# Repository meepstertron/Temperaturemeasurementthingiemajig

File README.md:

# Temperaturemeasurementthingimajig

That was a mouthful!

This is one of my first fully designed and hopefully made pcbs! :D

basically this is a small sensor node based on the readily availible CH32V003 which is a low cost (~20 cents!) risc-v MCU. it features a feature rich IO (well for 0.2usd it is). I am using the SHT4x chip to actually capture the environmental readings, because it is both accurate and fairly cost effective.

## Why should you care?

Honestly... You probably shouldnt, but for those who do want to know why: the whole node is open source meaning it can be re-mixed, re-branded and changed to your hearts content maybe even slap your logo or a silly cat on the silkscreen, it is also very cheap. running off a cr2032 and only costing about 3usd per node! Now compare that to the shelly series of Humid+Temp nodes...

## How is it so cheap??

I got it down to a nice value because i didnt use a expensive MCU like the ESP32 series (even though they are pretty effective in cost if you want wifi) but instead a cheaper and more bare bones MCU, since my project just didnt need it! a simple ASK/OOK transmitter instead of a costly variable or even wifi chip brought it down a lot as well. (we're talking cents but who cares)

## Bill of materials! (yall gotta foot the bill on this one :P /satire)
| Quantity | Component / Description | Package / Size | Estimated Cost (USD)
| :---: | :--- | :--- | :--- |
| **1x** | CR2032 Coin Cell Battery Holder | Through-Hole | 0.13 |
| **1x** | WCH CH32V003F4P6 Microcontroller | TSSOP-20 | 0.28 |
| **1x** | CMT2119A RF Transmitter | SOT-23-6 | 0.58 |
| **1x** | SHT4x Temperature & Humidity Sensor | DFN-4 | 0.95 |
| **1x** | 26MHz Crystal | SMD 3225 | 0.07 |
| **1x** | 868MHz Spring Antenna | Helical Spring | 0.23 |
| **1x** | Any color LED | 0805 | 0.02 |
| **2x** | 10k Ohm Resistor | 0805 | 0.004 |
| **1x** | 1k Ohm Resistor | 0805 | 0.004 |
| **1x** | 8.2nH Inductor | 0805 | 0.04 |
| **1x** | 100nH Inductor | 0805 | 0.04 |
| **1x** | 47uF Capacitor | 0805 | 0.22 |
| **2x** | 100nF (0.1uF) Capacitor | 0805 | 0.034 |
| **1x** | 82pF Capacitor | 0805 | 0.018 |
| **1x** | 3.9pF Capacitor | 0805 | 0.015 |

## AI...

I want to be as transparent as i can. I did use AI to help me scout components like the SHT40 instead of the AHT20 i was familiar with. i also used it for my rf, it called out my shitty meander (which i calculated as a microstrip, oops) which i then replaced with a more easier to work with coil antenna.
However i do not feel as if i used ai to a higher degree than 20% since i still did all of the design work, i wired up the schematic, i read the datasheets and i eventually designed the pcb.

## What programs were used
 - KiCad
 - Onshape

## Images :D

## Hackclub? 

This is a submission to hackclub's forge! Hackclub is a cool charity yall should go check them out!

## Contact me or sum

Email: jan.koch@hexagonical.ch

orrr:

@meepstertron on the hackclub slack!

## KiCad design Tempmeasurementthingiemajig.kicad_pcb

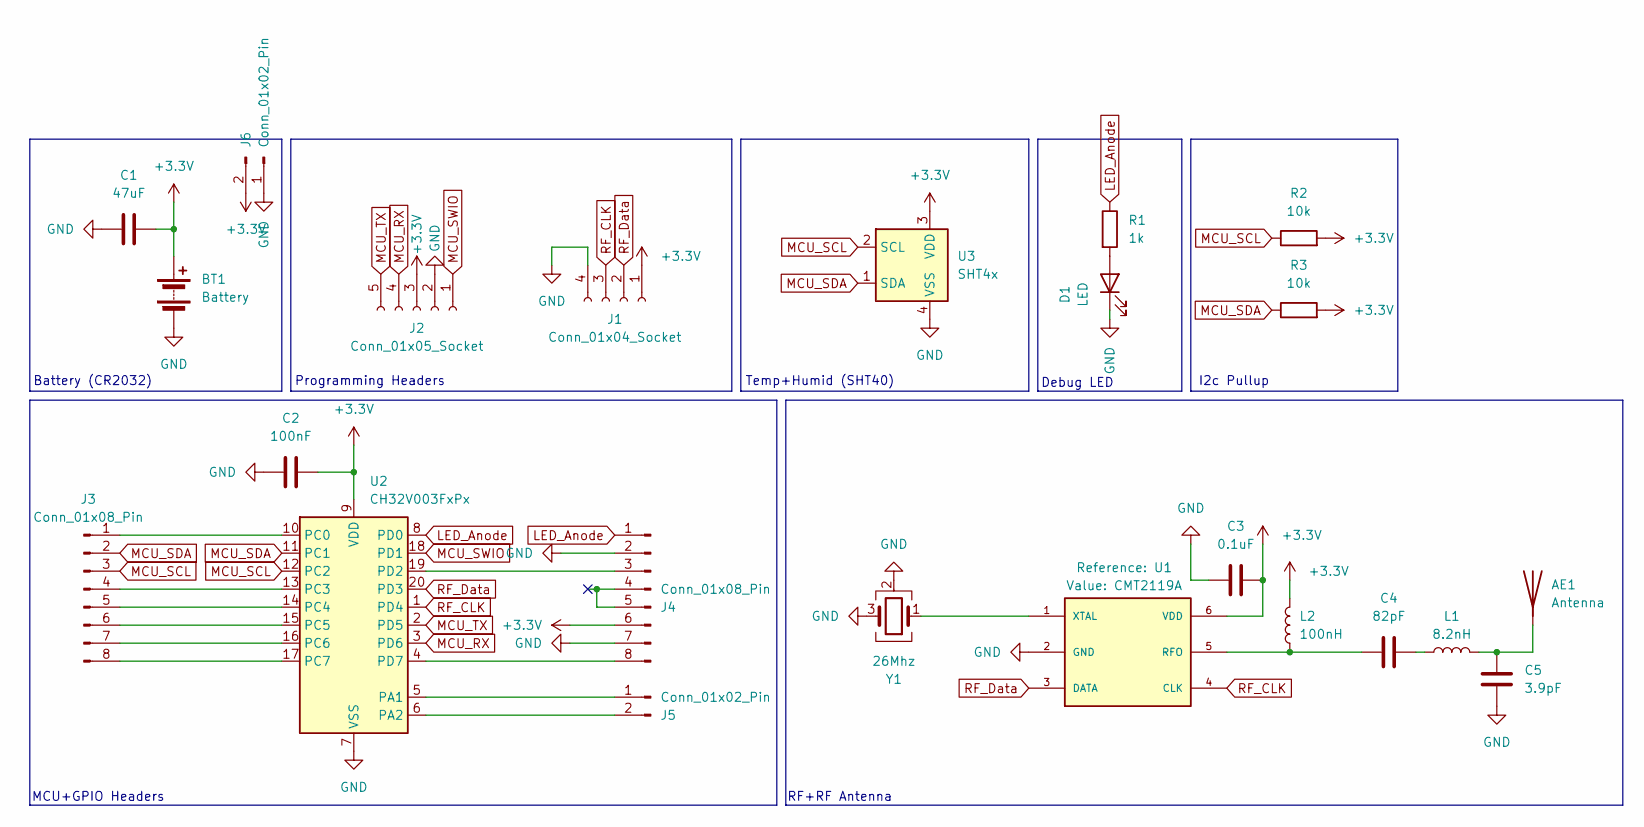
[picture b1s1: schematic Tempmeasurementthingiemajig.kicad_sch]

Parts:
AE1: Antenna
BT1: Battery; BAT-TH_MY-2032-06
C1: 47uF; C_0805_2012Metric_Pad1.18x1.45mm_HandSolder
C2: 100nF; C_0805_2012Metric_Pad1.18x1.45mm_HandSolder
C3: 0.1uF; C_0805_2012Metric_Pad1.18x1.45mm_HandSolder
C4: 82pF; C_0805_2012Metric_Pad1.18x1.45mm_HandSolder
C5: 3.9pF; C_0805_2012Metric_Pad1.18x1.45mm_HandSolder
D1: LED; LED_0805_2012Metric_Pad1.15x1.40mm_HandSolder
J1: Conn_01x04_Socket; PinHeader_1x04_P2.54mm_Vertical
J2: Conn_01x05_Socket; PinHeader_1x05_P2.54mm_Vertical
J3, J4: Conn_01x08_Pin; PinHeader_1x08_P2.54mm_Vertical
J5: Conn_01x02_Pin; PinHeader_1x02_P2.54mm_Vertical
J6: Conn_01x02_Pin; PinSocket_1x02_P2.54mm_Vertical
L1: 8.2nH; L_0805_2012Metric_Pad1.05x1.20mm_HandSolder
L2: 100nH; L_0805_2012Metric_Pad1.05x1.20mm_HandSolder
R1: 1k; R_0805_2012Metric_Pad1.20x1.40mm_HandSolder
R2, R3: 10k; R_0805_2012Metric_Pad1.20x1.40mm_HandSolder
U1: CMT2119A; SOT23-6
U2: CH32V003FxPx; TSSOP-20_4.4x6.5mm_P0.65mm
U3: SHT4x; Sensirion_DFN-4_1.5x1.5mm_P0.8mm_SHT4x_NoCentralPad
Y1: 26Mhz; Crystal_SMD_3225-4Pin_3.2x2.5mm

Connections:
+3.3V: BT1.1 (+), C1.2, C2.2, C3.2, J1.1, J2.3, J4.6, J6.2, L2.2, R2.2, R3.2, U1.6 (VDD), U2.9 (VDD), U3.3 (VDD)
GND: BT1.2 (-), C1.1, C2.1, C3.1, C5.1, D1.1 (K), J1.4, J2.2, J4.2, J4.7, J6.1, U1.2 (GND), U2.7 (VSS), U3.4 (VSS), Y1.2 (G), Y1.3, Y1.4 (G)
LED_Anode: J4.1, R1.1, U2.8 (PD0)
MCU_RX: J2.4, U2.3 (PD6)
MCU_SCL: J3.3, R2.1, U2.12 (PC2), U3.2 (SCL)
MCU_SDA: J3.2, R3.1, U2.11 (PC1), U3.1 (SDA)
MCU_SWIO: J2.1, U2.18 (PD1)
MCU_TX: J2.5, U2.2 (PD5)
unnamed: AE1.1, C5.2, L1.2
unnamed: C4.2, L1.1
unnamed: D1.2 (A), R1.2
unnamed: J3.1, U2.10 (PC0)
unnamed: J3.4, U2.13 (PC3)
unnamed: J3.5, U2.14 (PC4)
unnamed: J3.6, U2.15 (PC5)
unnamed: J3.7, U2.16 (PC6)
unnamed: J3.8, U2.17 (PC7)
unnamed: J4.3, U2.19 (PD2)
unnamed: J4.8, U2.4 (PD7)
unnamed: J5.1, U2.5 (PA1)
unnamed: J5.2, U2.6 (PA2)
unnamed: C4.1, L2.1, U1.5 (RFO)
unnamed: U1.1 (XTAL), Y1.1
RF_CLK: J1.3, U1.4 (CLK), U2.1 (PD4)
RF_Data: J1.2, U1.3 (DATA), U2.20 (PD3)

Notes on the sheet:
I2c Pullup
Programming Headers
RF+RF Antenna
MCU+GPIO Headers
Temp+Humid (SHT40)
Debug LED
Battery (CR2032)

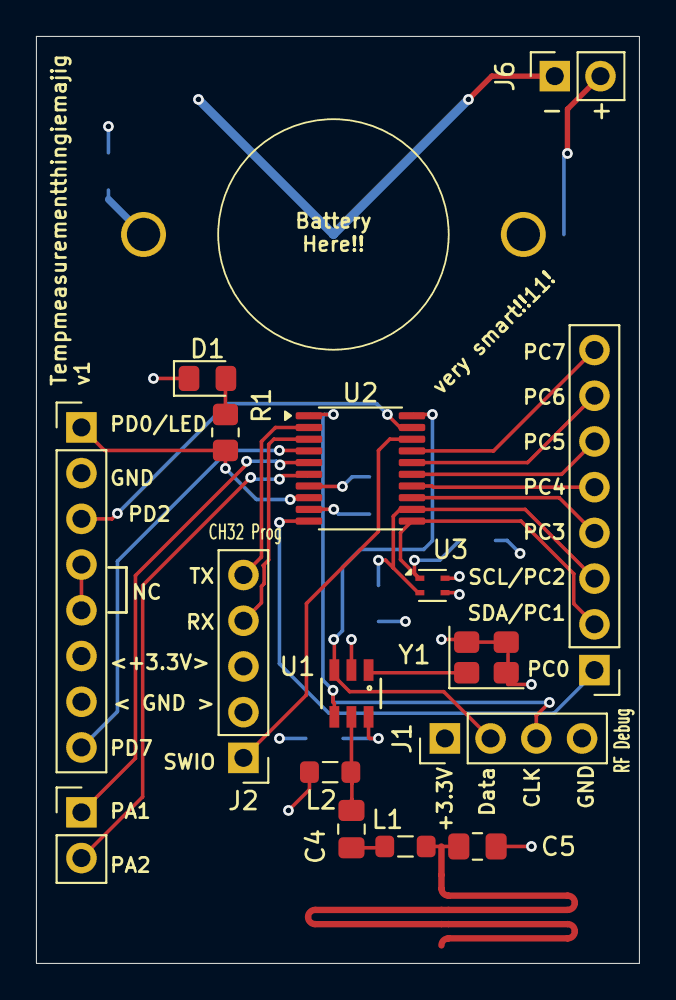
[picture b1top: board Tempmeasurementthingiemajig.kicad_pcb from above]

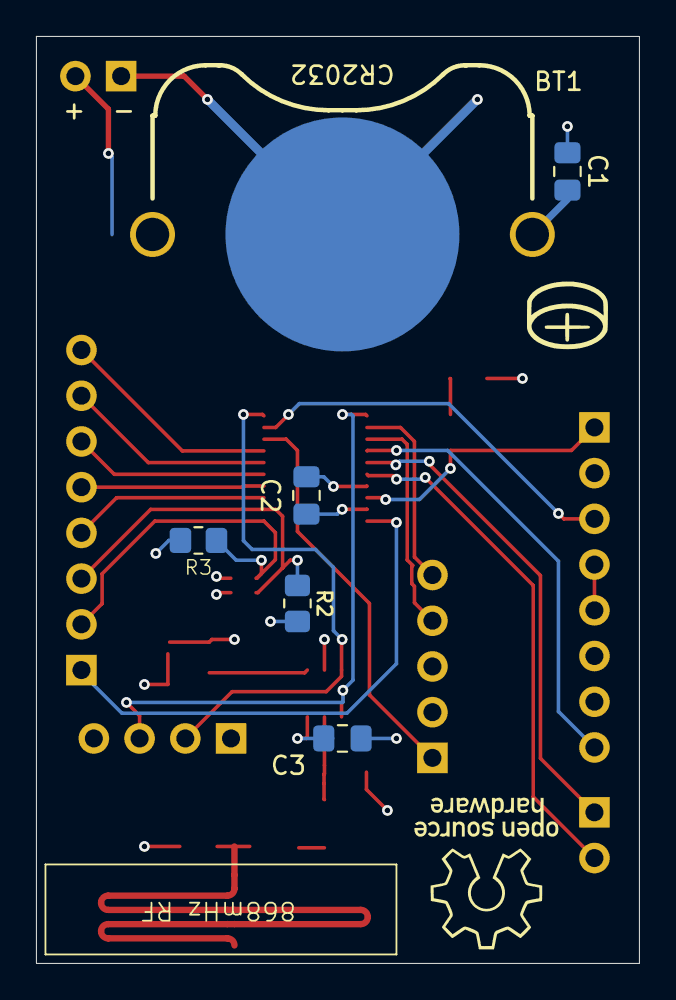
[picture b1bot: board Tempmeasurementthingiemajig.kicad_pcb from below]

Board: 4 copper layers, 33.5 x 51.5 mm, 22 parts (6 on the bottom side), 25 nets.

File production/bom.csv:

Designator,Footprint,Quantity,Value,LCSC Part #
BT1,BAT-TH_MY-2032-06,1,Battery,C964823
C1,0805,1,47uF,
C2,0805,1,100nF,
C3,0805,1,0.1uF,
C4,0805,1,82pF,
C5,0805,1,3.9pF,
D1,0805,1,LED,
J1,PinHeader_1x04_P2.54mm_Vertical,1,Conn_01x04_Socket,
J2,PinHeader_1x05_P2.54mm_Vertical,1,Conn_01x05_Socket,
"J3, J4",PinHeader_1x08_P2.54mm_Vertical,2,Conn_01x08_Pin,
J5,PinHeader_1x02_P2.54mm_Vertical,1,Conn_01x02_Pin,
J6,PinSocket_1x02_P2.54mm_Vertical,1,Conn_01x02_Pin,
L1,0805,1,8.2nH,
L2,0805,1,100nH,
R1,0805,1,1k,
"R2, R3",0805,2,10k,
U1,SOT23-6,1,CMT2119A,
U2,TSSOP-20_4.4x6.5mm_P0.65mm,1,CH32V003FxPx,
U3,Sensirion_DFN-4_1.5x1.5mm_P0.8mm_SHT4x_NoCentralPad,1,SHT4x,
Y1,Crystal_SMD_3225-4Pin_3.2x2.5mm,1,26Mhz,
AN1,Antenna_Helical_Spring,1,868MHz
